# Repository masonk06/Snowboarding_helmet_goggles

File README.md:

# Snowboarding_helmet_goggles

SnowLens-inspired experimental heads-up display for snowboarding. Two small OLEDs are intended to show concise ride telemetry, with an ESP32-S3 collecting sensor data and a XIAO RP2040 driving the displays.

## Current progress — November 6, 2026

The main electronics are owned. Architecture, remaining parts, and implementation phases are documented below. No working firmware, assembled wiring, validated optics, runtime measurements, or on-snow results have been supplied or verified. This snapshot records design progress; it does not claim a working AR product or affiliation with SnowLens.

| Confirmed owned part | Qty | Intended role |
| --- | ---: | --- |
| Waveshare 1.51-inch OLED | 2 | Left/right HUD displays; prior discussion identifies the transparent model, exact revision to verify |
| Seeed Studio XIAO RP2040 | 1 | Display controller |
| ESP32-S3 development board | 1 | Sensor acquisition and telemetry; exact board variant to record |
| NEO-6M GPS module | 1 | Position and ground speed |
| MPU6050 module | 1 | Acceleration and angular velocity |
| BMP280 module | 1 | Pressure, sensor temperature, relative altitude estimate |

## Project documents

- [Architecture and technical caveats](docs/ARCHITECTURE.md)
- [Owned inventory and remaining BOM](docs/BOM.md)
- [Phased implementation and acceptance checks](docs/ROADMAP.md)
- [Revision-A two-board PCB prototype](docs/PCB_PROTOTYPE.md)
- [KiCad project: rev 0.2 bench carrier PCBs](hardware/kicad/README.md): schematic, routed two-board layout, Gerbers, pin maps and cable wiring
- [**Option: connection via Bluetooth / wireless**](hardware/option-bluetooth-wireless/README.md): separate alternative design with no goggle-jacket cable. XIAO ESP32S3 + LiPo at the goggles, radio link via ESP-NOW or Bluetooth LE.

### Hardware folders

| Folder | Design | Link between goggles and jacket |
| --- | --- | --- |
| `hardware/kicad/` | Cable version, rev 0.2 | 4-wire JST-PH cable (UART + 5 V) |
| `hardware/option-bluetooth-wireless/` | **Wireless option**, rev W0.1 | Radio (ESP-NOW / Bluetooth LE), goggle battery |

Choose one for a build. Both share the same OLED, sensor and jacket-board wiring.

## Update — November 19, 2026

Added a KiCad 10 project in `hardware/kicad/`. It contains the bench schematic, now with cable connectors, and a routed 2-layer layout for a **goggle carrier** (XIAO RP2040 + two OLED headers) and a **jacket carrier** (ESP32-S3-DevKitC-1 + NEO-6M / MPU6050 / BMP280 sockets). The two boards are joined by a 4-wire JST-PH cable. ERC and DRC pass with zero issues, and fab files are included. Header spacings and module pinouts still need to be measured on the owned boards before ordering. This bench carrier does not yet include the RS-485 tether and protection specified for revision A.

Start with USB-powered bench tests, one OLED and one sensor at a time. Record board revisions and verify module pinouts and voltage requirements before wiring. Final pin assignments and battery selection remain open.

## Prototype boundaries

Transparent OLEDs alone do not form a focused near-eye image. Optical feasibility, daylight contrast, field of view, eye relief, and binocular comfort must be demonstrated before committing to mounts. GPS outages cannot be bridged accurately by simply integrating the MPU6050. Keep invalid or stale measurements visibly distinct from valid telemetry.

The prototype must preserve vision and the protective function of goggles and helmet. Begin with stationary fit checks and controlled tests; it is not navigation or safety equipment.

## Primary hardware references

- [Waveshare 1.51-inch transparent OLED wiki](https://www.waveshare.com/wiki/1.51inch_Transparent_OLED) — candidate model, SPI/I2C configuration and vendor examples.
- [Seeed XIAO RP2040 documentation](https://wiki.seeedstudio.com/XIAO-RP2040/) — identify the actual board revision, pinout and power arrangement; standard and Plus variants differ.

Use the documentation and schematic for each exact purchased breakout before selecting wiring or power hardware. No firmware build or automated test suite exists in this documentation snapshot.

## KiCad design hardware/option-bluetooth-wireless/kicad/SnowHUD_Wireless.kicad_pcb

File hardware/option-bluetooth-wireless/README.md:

# Option: connection via Bluetooth / wireless (rev W0.1)

> **This folder is an alternative design, kept separate from the cable version.**
> The cable (tether) version lives in [`hardware/kicad/`](../kicad/README.md) and is unchanged.
> Pick **one** of the two for a build.

In this option the goggles and jacket have **no cable between them**. Both ends use an ESP32-S3 radio:

- **Jacket:** the ESP32-S3-DevKitC-1 you already own. It has Bluetooth LE and Wi-Fi built in.
- **Goggles:** the XIAO RP2040, which has no radio, is replaced by a **Seeed XIAO ESP32S3**. It has the same 14-pin XIAO size and layout, plus a built-in radio and LiPo charger.
- The goggles get their own small **LiPo battery**, on/off switch and battery-voltage monitor.

## Cable vs. wireless at a glance

| | Cable version (`hardware/kicad`, rev 0.2) | Wireless option (this folder, rev W0.1) |
| --- | --- | --- |
| Goggle controller | XIAO RP2040 | **XIAO ESP32S3** (new part) |
| Goggle ↔ jacket link | 4-wire JST-PH cable, 3.3 V UART | **Radio: ESP-NOW (recommended) or Bluetooth LE** |
| Goggle power | 5 V over the cable (JP1) or USB | **Own 1S LiPo** (charged by the XIAO over USB-C) |
| Goggle board | 30.5 × 29.5 mm | 30.5 × 32.5 mm (+3 mm for battery parts) |
| Jacket board | ESP32 + sensors + J4 cable connector | Same, **without** J4 |
| Batteries to charge | 1 (jacket, still to be designed) | 2 (goggle LiPo + jacket) |

## Which radio protocol?

The ESP32-S3 on both ends supports both:

- **ESP-NOW (recommended for goggle ↔ jacket):** Espressif's direct board-to-board packets. No pairing or router, very low latency, small payloads (≤250 bytes), which is ideal for sending speed, altitude etc. ~10×/s.
- **Bluetooth LE:** the standard option, also usable to talk to a **phone app** later. It needs pairing and has more protocol overhead.

ESP-NOW and BLE can coexist on the jacket ESP32 (for example ESP-NOW to the goggles, BLE to a phone). The hardware is identical for either; the choice is purely firmware.

## New parts for this option

These are in addition to the parts you already own. Full list: [`BOM.md`](BOM.md).

| Ref | Part | Qty | Notes |
| --- | --- | ---: | --- |
| U1 | **Seeed Studio XIAO ESP32S3** (not the "Sense" camera version) | 1 | Replaces the XIAO RP2040 on the goggle board. Comes with a U.FL antenna; **fit the antenna**. |
| J5 + battery | 1S 3.7 V LiPo with JST-PH 2.0 plug, ~300–500 mAh | 1 | e.g. 502535 (~5 × 25 × 35 mm, ~400 mAh). **Check plug polarity** (see below). |
| SW1 | C&K OS102011MS2Q slide switch (SPDT, THT) | 1 | Battery on/off |
| R1, R2 | 220 kΩ 0603 resistor | 2 | Battery divider (VBAT/2 → D5) |
| C1 | 100 nF 0603 capacitor | 1 | ADC filter |
| TP1, TP2 | Bare wire pads on the PCB | — | Nothing to buy. Two short wires to the XIAO's underside battery pads. |

The XIAO RP2040 is not needed for this option. Keep it for the cable version or for bench testing.

## How the goggle power works

```text
LiPo ──J5── BAT_RAW ──SW1── VBAT ──TP1 (B+)─wire─► XIAO ESP32S3 underside BAT+ pad
                              │                    (XIAO's built-in charger charges the LiPo from USB-C)
                              ├─R1 220k─┬─► D5 (GPIO6, ADC1) = VBAT/2
                              │         ├─R2 220k─ GND
                              │         └─C1 100nF─ GND
GND ─────────────────────────TP2 (B-)─wire─► XIAO underside BAT- pad
```

- The XIAO ESP32S3's battery connection is two **pads on its underside**, not header pins. TP1/TP2 sit right below the XIAO on the carrier: solder a short wire from each up to the XIAO's BAT+ / BAT− pads. Do this before soldering the XIAO onto its headers, and keep the wires clear of the header pins.
- **SW1 OFF disconnects the battery completely.** That means the LiPo **cannot charge while the switch is off**. Turn it on to charge from USB-C.
- **Battery monitor:** read D5 with the ADC and multiply by 2 for the battery voltage. The divider draws only ~9.5 µA, and nothing at all when SW1 is off.
- ⚠️ **LiPo polarity:** JST-PH battery leads are **not standardised**. Some batteries are wired the opposite way to others. Before plugging in, check with a meter that the red wire lands on the pad marked **B+/pin 1** (square pad of J5). Swap the pins in the plug housing if needed.

## Goggle board pin map (XIAO ESP32S3)

The OLED wiring is the same as the cable version, so OLED firmware can be shared.

| XIAO pin | ESP32-S3 GPIO | Net | Goes to |
| --- | --- | --- | --- |
| D0 | GPIO1 | `OLED_CS_L` | DS1 pin 5 |
| D1 | GPIO2 | `OLED_CS_R` | DS2 pin 5 |
| D2 | GPIO3 | `OLED_DC` | DS1 / DS2 pin 6 |
| D3 | GPIO4 | `OLED_RST` | DS1 / DS2 pin 7 |
| D5 | GPIO6 | `VBAT_SENSE` | R1/R2 divider (VBAT/2) |
| D8 / SCK | GPIO7 | `SPI_SCK` | DS1 / DS2 pin 4 |
| D10 / MOSI | GPIO9 | `SPI_MOSI` | DS1 / DS2 pin 3 |
| 3V3 | — | `+3V3_XIAO` | DS1 / DS2 pin 1 |
| GND | — | `GND_HUD` | DS1 / DS2 pin 2, J5, TP2 |
| D4, D6, D7, D9, 5V | — | unused | D4 free for a "blank display" button; D6/D7 (old cable UART) free |

> GPIO3 (D2) is an ESP32-S3 strapping pin (JTAG source select). Using it as the OLED DC output after boot is normally fine. If the board ever boots strangely with the OLEDs connected, move DC to the free D4.

## Jacket board

Identical to the cable version's jacket board ([pin map](../kicad/README.md#jacket-board)), except that **J4 is removed**. ESP32 GPIO4/GPIO5, which carried the cable UART, are now unused. The jacket is still powered from the DevKit's USB; the jacket battery stage is still an open item in [`docs/PCB_PROTOTYPE.md`](../../docs/PCB_PROTOTYPE.md).

## Antenna and placement notes

- Fit the U.FL antenna supplied with the XIAO ESP32S3 and route it **away from metal, carbon fibre, the battery and your head** where possible, e.g. along the outside of the goggle strap.
- The jacket DevKit's PCB antenna is at the 3V3/"ANT" end of the board. Don't bury it in a metal enclosure or right against the battery.
- Bodies absorb 2.4 GHz well. Over the ~0.5–1 m helmet-to-jacket distance ESP-NOW should be fine, but **test the link worn**, with both units in their enclosures, before trusting it.

## Battery runtime (estimate only, measure it)

Two OLEDs plus the ESP32-S3 with its radio might draw very roughly 80–150 mA, which would be about 2–4 h on a 400 mAh cell. That's less in the cold, because LiPos lose much of their capacity below freezing. Per the [roadmap](../../docs/ROADMAP.md), measure the real current before choosing the battery. Keeping the battery in a strap pouch close to the head helps in the cold. Ways to save power: lower OLED brightness, a lower ESP-NOW send rate, and light-sleep between updates.

## Files

| Path | What it is |
| --- | --- |
| `kicad/SnowHUD_Wireless.kicad_pro` | KiCad 10 project (open this) |
| `kicad/SnowHUD_Wireless.kicad_sch` / `_schematic.pdf` | Schematic rev W0.1 |
| `kicad/SnowHUD_Wireless.kicad_pcb` | Routed 2-layer layout, both boards in one file |
| `kicad/SnowHUD_Wireless.kicad_sym`, `SnowHUD_Wireless.pretty/` | This option's own symbol and footprint libraries (incl. the new XIAO ESP32S3) |
| `kicad/fab/SnowHUD_Wireless_W0.1_gerbers.zip` | Gerbers + drill (both boards) |
| `kicad/fab/SnowHUD_Wireless_bom.csv` | BOM exported from the schematic |
| `kicad/fab/SnowHUD_Wireless_positions.csv` | Component positions (for assembly services) |
| `kicad/fab/drc_report.txt`, `erc_report.txt` | 0 DRC violations / 0 unconnected / 0 parity issues; 0 ERC issues |
| `kicad/images/` | Top, bottom and 3D renders |
| `kicad/scripts/gen_sch.py` | Generates the schematic (reuses module symbols from the cable version) |
| `kicad/scripts/make_fp.py`, `build_pcb.py` | Footprints; placement + routing + pours (overwrites the PCB) |

Regenerate everything:

```powershell
cd hardware\option-bluetooth-wireless\kicad\scripts
$py  = "C:\Program Files\KiCad\10.0\bin\python.exe"
$cli = "C:\Program Files\KiCad\10.0\bin\kicad-cli.exe"
& $py gen_sch.py
& $py make_fp.py
& $cli sch export netlist --format kicadsexpr -o SnowHUD_Wireless.net ..\SnowHUD_Wireless.kicad_sch
& $py build_pcb.py SnowHUD_Wireless.net
& $cli pcb drc --schematic-parity --refill-zones -o drc.txt ..\SnowHUD_Wireless.kicad_pcb
```

`gen_sch.py` overwrites the schematic. Once you start editing the schematic by hand in KiCad, stop using it.

## Verify before ordering

- [ ] Everything in the cable version's [checklist](../kicad/README.md#verify-before-ordering): ESP32 row spacing (22.86 mm), XIAO row spacing (15.24 mm), module pin orders, module body clearance.
- [ ] XIAO ESP32S3 pin labels match the table above (check the [Seeed XIAO ESP32S3 wiki](https://wiki.seeedstudio.com/xiao_esp32s3_getting_started/)), and the location of its underside BAT pads relative to TP1/TP2.
- [ ] LiPo plug polarity matches J5 (pin 1 = B+, square pad).
- [ ] Battery and switch fit within the goggle strap mount.
- [ ] Radio link tested while worn (body blocking, cold, inside enclosures).
- [ ] Measured current and runtime are acceptable.

## Status

Design only. Nothing in this option has been built or tested. Firmware for ESP-NOW/BLE does not exist yet.

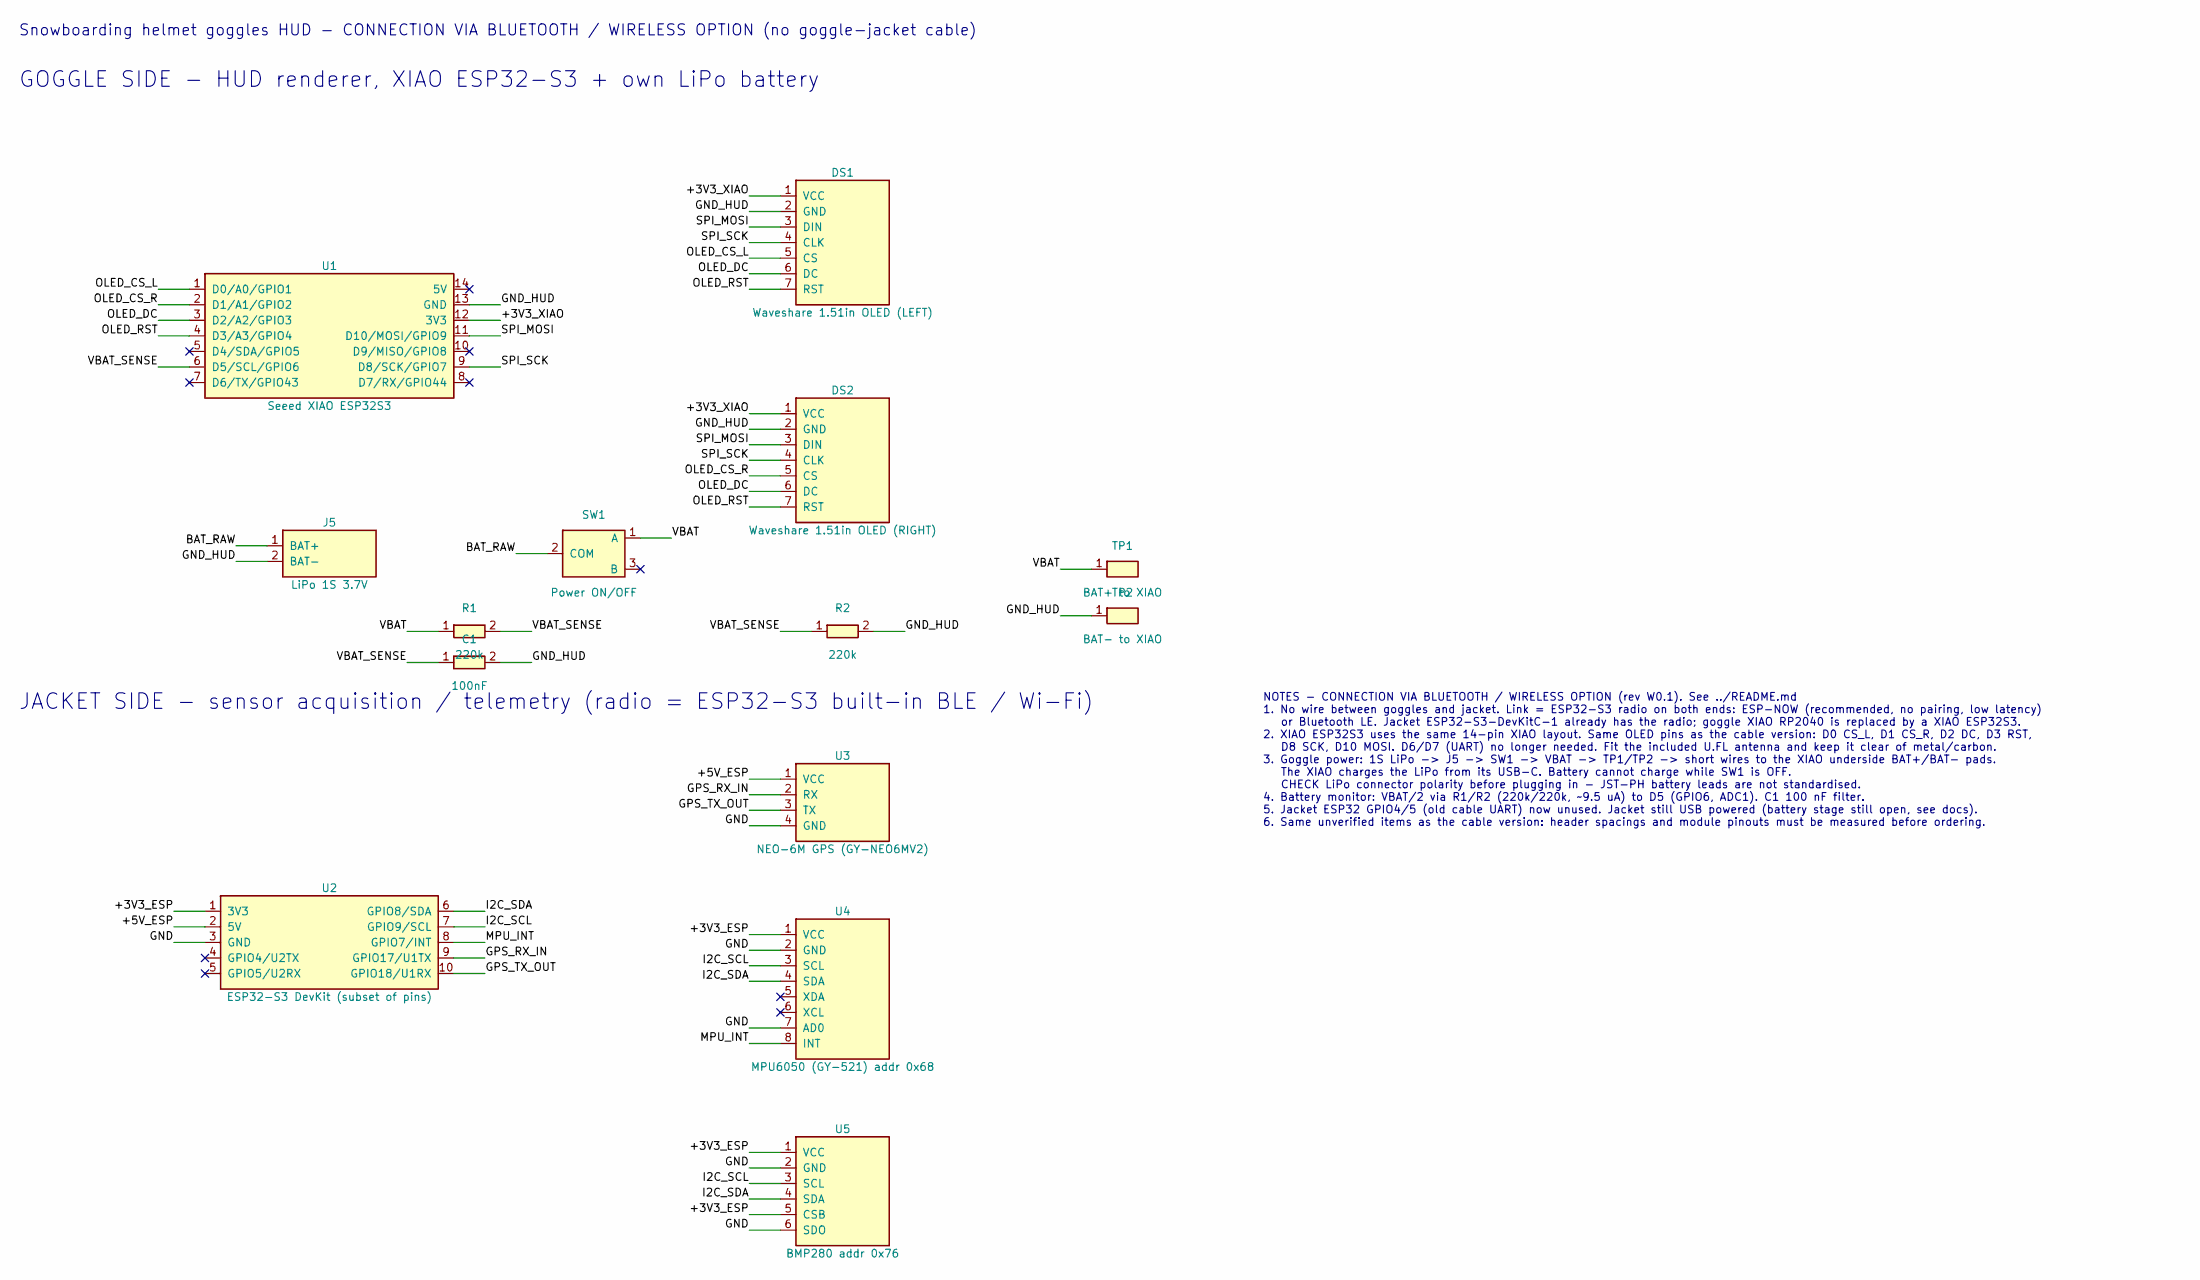
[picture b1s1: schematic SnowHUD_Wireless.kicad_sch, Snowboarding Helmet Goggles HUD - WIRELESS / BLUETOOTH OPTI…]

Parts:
C1: 100nF; C_0603_1608Metric
DS1: Waveshare 1.51in OLED (LEFT); PinHeader_1x07_P2.54mm_Vertical
DS2: Waveshare 1.51in OLED (RIGHT); PinHeader_1x07_P2.54mm_Vertical
J5: LiPo 1S 3.7V; JST_PH_B2B-PH-K_1x02_P2.00mm_Vertical
R1, R2: 220k; R_0603_1608Metric
SW1: Power ON/OFF; SW_Slide_SPDT_Straight_CK_OS102011MS2Q
TP1: BAT+ to XIAO; TestPoint_THTPad_D2.0mm_Drill1.0mm
TP2: BAT- to XIAO; TestPoint_THTPad_D2.0mm_Drill1.0mm
U1: Seeed XIAO ESP32S3; XIAO_ESP32S3_THT
U2: ESP32-S3 DevKit (subset of pins); ESP32-S3-DevKitC-1_Socket
U3: NEO-6M GPS (GY-NEO6MV2); PinSocket_1x04_P2.54mm_Vertical
U4: MPU6050 (GY-521) addr 0x68; PinSocket_1x08_P2.54mm_Vertical
U5: BMP280 addr 0x76; PinSocket_1x06_P2.54mm_Vertical

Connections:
/+3V3_ESP: U2.1 (3V3), U4.1 (VCC), U5.1 (VCC), U5.5 (CSB)
/+3V3_XIAO: DS1.1 (VCC), DS2.1 (VCC), U1.12 (3V3)
/+5V_ESP: U2.2 (5V), U3.1 (VCC)
/BAT_RAW: J5.1 (BAT+), SW1.2 (COM)
/GND: U2.3 (GND), U3.4 (GND), U4.2 (GND), U4.7 (AD0), U5.2 (GND), U5.6 (SDO)
/GND_HUD: C1.2, DS1.2 (GND), DS2.2 (GND), J5.2 (BAT-), R2.2, TP2.1, U1.13 (GND)
/GPS_RX_IN: U2.9 (GPIO17/U1TX), U3.2 (RX)
/GPS_TX_OUT: U2.10 (GPIO18/U1RX), U3.3 (TX)
/I2C_SCL: U2.7 (GPIO9/SCL), U4.3 (SCL), U5.3 (SCL)
/I2C_SDA: U2.6 (GPIO8/SDA), U4.4 (SDA), U5.4 (SDA)
/MPU_INT: U2.8 (GPIO7/INT), U4.8 (INT)
/OLED_CS_L: DS1.5 (CS), U1.1 (D0/A0/GPIO1)
/OLED_CS_R: DS2.5 (CS), U1.2 (D1/A1/GPIO2)
/OLED_DC: DS1.6 (DC), DS2.6 (DC), U1.3 (D2/A2/GPIO3)
/OLED_RST: DS1.7 (RST), DS2.7 (RST), U1.4 (D3/A3/GPIO4)
/SPI_MOSI: DS1.3 (DIN), DS2.3 (DIN), U1.11 (D10/MOSI/GPIO9)
/SPI_SCK: DS1.4 (CLK), DS2.4 (CLK), U1.9 (D8/SCK/GPIO7)
/VBAT: R1.1, SW1.1 (A), TP1.1
/VBAT_SENSE: C1.1, R1.2, R2.1, U1.6 (D5/SCL/GPIO6)

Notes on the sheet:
Snowboarding helmet goggles HUD - CONNECTION VIA BLUETOOTH / WIRELESS OPTION (no goggle-jacket cable)
GOGGLE SIDE - HUD renderer, XIAO ESP32-S3 + own LiPo battery
JACKET SIDE - sensor acquisition / telemetry (radio = ESP32-S3 built-in BLE / Wi-Fi)
NOTES - CONNECTION VIA BLUETOOTH / WIRELESS OPTION (rev W0.1). See ../README.md 1. No wire between goggles and jacket. Link = ESP32-S3 radio on both ends: ESP-NOW (recommended, no pairing, low latency) or Bluetooth LE. Jacket ESP32-S3-DevKitC-1 already has the radio; goggle XIAO RP2040 is replaced 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

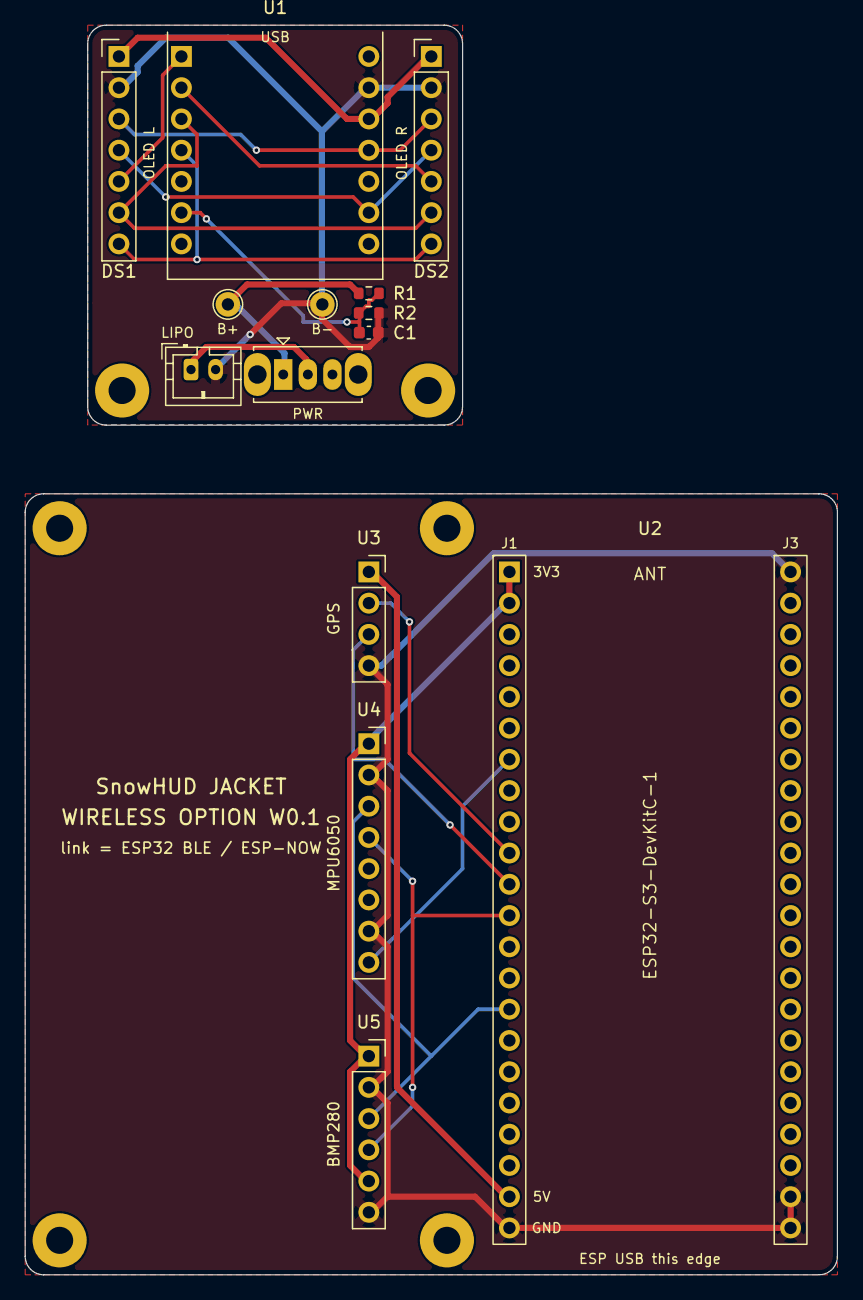
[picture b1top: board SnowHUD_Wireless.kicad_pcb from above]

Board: 2 copper layers, 66.0 x 101.6 mm, 20 parts (0 on the bottom side), 19 nets.

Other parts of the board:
H1, H2, H3, H4, H5, H6: M2; MountingHole_2.2mm_M2_Pad

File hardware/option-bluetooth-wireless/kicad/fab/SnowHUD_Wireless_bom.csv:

"Reference","Value","Footprint","Description","QUANTITY"
"C1","100nF","Capacitor_SMD:C_0603_1608Metric","ADC filter","1"
"DS1","Waveshare 1.51in OLED (LEFT)","Connector_PinHeader_2.54mm:PinHeader_1x07_P2.54mm_Vertical","Left HUD display, 4-wire SPI mode","1"
"DS2","Waveshare 1.51in OLED (RIGHT)","Connector_PinHeader_2.54mm:PinHeader_1x07_P2.54mm_Vertical","Right HUD display, 4-wire SPI mode","1"
"J5","LiPo 1S 3.7V","Connector_JST:JST_PH_B2B-PH-K_1x02_P2.00mm_Vertical","Goggle battery, JST-PH 2-pin. CHECK battery lead polarity - not standardised!","1"
"R1,R2","220k","Resistor_SMD:R_0603_1608Metric","Battery divider bottom,Battery divider top","2"
"SW1","Power ON/OFF","Button_Switch_THT:SW_Slide_SPDT_Straight_CK_OS102011MS2Q","Slide switch in battery + lead (battery cannot charge while OFF)","1"
"U1","Seeed XIAO ESP32S3","SnowHUD_Wireless:XIAO_ESP32S3_THT","Display controller + radio (BLE 5 / Wi-Fi / ESP-NOW). Built-in LiPo charger on underside BAT pads.","1"
"U2","ESP32-S3 DevKit (subset of pins)","SnowHUD_Wireless:ESP32-S3-DevKitC-1_Socket","Sensor acquisition + radio link to goggles","1"
"U3","NEO-6M GPS (GY-NEO6MV2)","Connector_PinSocket_2.54mm:PinSocket_1x04_P2.54mm_Vertical","GPS, UART 9600 baud default","1"
"U4","MPU6050 (GY-521) addr 0x68","Connector_PinSocket_2.54mm:PinSocket_1x08_P2.54mm_Vertical","6-axis IMU","1"
"U5","BMP280 addr 0x76","Connector_PinSocket_2.54mm:PinSocket_1x06_P2.54mm_Vertical","Barometer, I2C mode (CSB high)","1"

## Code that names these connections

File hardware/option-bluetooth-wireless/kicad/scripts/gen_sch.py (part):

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
# XIAO ESP32-S3: same 14-pin layout and numbering as the XIAO RP2040 symbol, ESP32-S3 pin names
x = rename(blocks["XIAO_RP2040"], "XIAO_RP2040", "XIAO_ESP32S3")
for old, new in [("D0/A0/P26", "D0/A0/GPIO1"), ("D1/A1/P27", "D1/A1/GPIO2"), ("D2/A2/P28", "D2/A2/GPIO3"),
                 ("D3/A3/P29", "D3/A3/GPIO4"), ("D4/SDA/P6", "D4/SDA/GPIO5"), ("D5/SCL/P7", "D5/SCL/GPIO6"),
                 ("D6/TX/P0", "D6/TX/GPIO43"), ("D7/RX/P1", "D7/RX/GPIO44"), ("D8/SCK/P2", "D8/SCK/GPIO7"),
                 ("D9/MISO/P4", "D9/MISO/GPIO8"), ("D10/MOSI/P3", "D10/MOSI/GPIO9"),
                 ('(property "Value" "XIAO_RP2040"', '(property "Value" "XIAO_ESP32S3"')]:
    assert old in x, old
    x = x.replace(old, new)
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     "3. Goggle power: 1S LiPo -> J5 -> SW1 -> VBAT -> TP1/TP2 -> short wires to the XIAO underside BAT+/BAT- pads.\n"
     "   The XIAO charges the LiPo from its USB-C. Battery cannot charge while SW1 is OFF.\n"
     "   CHECK LiPo connector polarity before plugging in - JST-PH battery leads are not standardised.\n"
     "4. Battery monitor: VBAT/2 via R1/R2 (220k/220k, ~9.5 uA) to D5 (GPIO6, ADC1). C1 100 nF filter.\n"
     "5. Jacket ESP32 GPIO4/5 (old cable UART) now unused. Jacket still USB powered (battery stage still open, see docs).\n"
     "6. Same unverified items as the cable version: header spacings and module pinouts must be measured before ordering.",
     228.6, 124.46)

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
